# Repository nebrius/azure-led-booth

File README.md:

# Azure LED Booth

An LED art piece for conference booths that attendees can control from Azure. This project is, in part, based on @nebrius [Raver Lights](https://github.com/nebrius/raver-lights) project.

This project touches on a few other repos of interest:

- https://github.com/nebrius/rvl-node-animations A helper library for creating animations
- TODO: starter repo link

# License

MIT License

Copyright (c) Bryan Hughes <bryan@nebri.us>

Permission is hereby granted, free of charge, to any person obtaining a copy
of this software and associated documentation files (the "Software"), to deal
in the Software without restriction, including without limitation the rights
to use, copy, modify, merge, publish, distribute, sublicense, and/or sell
copies of the Software, and to permit persons to whom the Software is
furnished to do so, subject to the following conditions:

The above copyright notice and this permission notice shall be included in all
copies or substantial portions of the Software.

THE SOFTWARE IS PROVIDED "AS IS", WITHOUT WARRANTY OF ANY KIND, EXPRESS OR
IMPLIED, INCLUDING BUT NOT LIMITED TO THE WARRANTIES OF MERCHANTABILITY,
FITNESS FOR A PARTICULAR PURPOSE AND NONINFRINGEMENT. IN NO EVENT SHALL THE
AUTHORS OR COPYRIGHT HOLDERS BE LIABLE FOR ANY CLAIM, DAMAGES OR OTHER
LIABILITY, WHETHER IN AN ACTION OF CONTRACT, TORT OR OTHERWISE, ARISING FROM,
OUT OF OR IN CONNECTION WITH THE SOFTWARE OR THE USE OR OTHER DEALINGS IN THE
SOFTWARE.

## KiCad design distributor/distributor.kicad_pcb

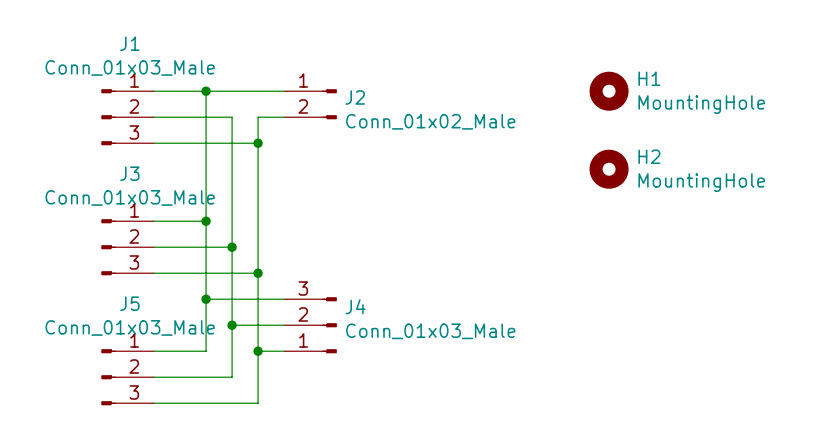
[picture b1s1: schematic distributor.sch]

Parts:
H1, H2: MountingHole; MountingHole_3.7mm
J1, J3, J5: Conn_01x03_Male; JST_VH_S3P-VH_1x03_P3.96mm_Horizontal
J2: Conn_01x02_Male; JST_VH_S2P-VH_1x02_P3.96mm_Horizontal
J4: Conn_01x03_Male; PinHeader_1x03_P2.54mm_Horizontal

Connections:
unnamed: J1.1, J2.1, J3.1, J4.3, J5.1
unnamed: J1.2, J3.2, J4.2, J5.2
unnamed: J1.3, J2.2, J3.3, J4.1, J5.3

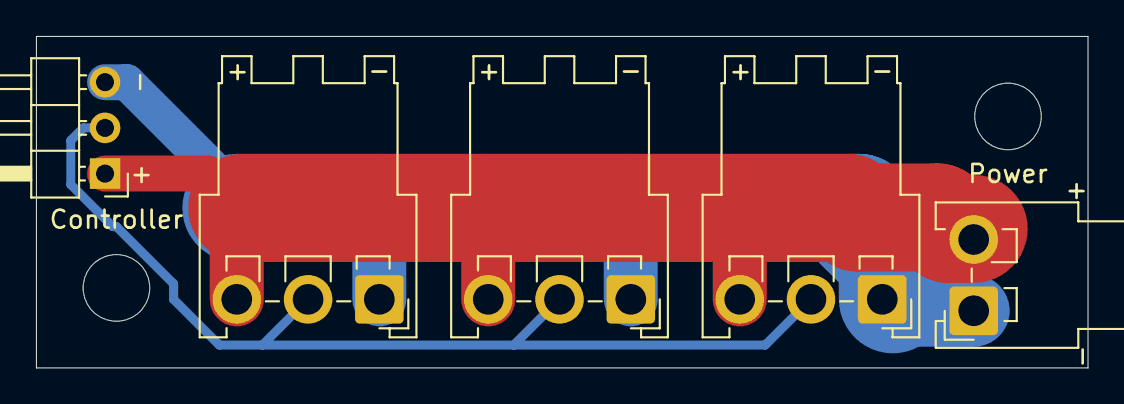
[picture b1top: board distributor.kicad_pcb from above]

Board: 2 copper layers, 58.4 x 18.4 mm, 7 parts (0 on the bottom side), 3 nets.

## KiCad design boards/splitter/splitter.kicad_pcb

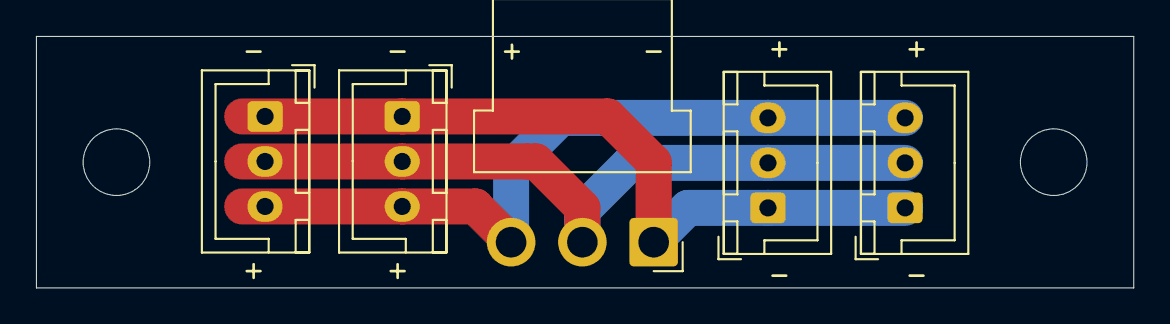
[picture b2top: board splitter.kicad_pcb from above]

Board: 2 copper layers, 61.0 x 14.0 mm, 7 parts (0 on the bottom side), 3 nets.

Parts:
H1, H2: MountingHole; MountingHole_3.7mm
J1, J2, J4, J5: Conn_01x03_Male; JST_XH_B3B-XH-A_1x03_P2.50mm_Vertical
J3: Conn_01x03_Male; JST_VH_B3PS-VH_1x03_P3.96mm_Horizontal

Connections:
unnamed: J1.1, J2.1, J3.1, J4.1, J5.1
unnamed: J1.2, J2.2, J3.2, J4.2, J5.2
unnamed: J1.3, J2.3, J3.3, J4.3, J5.3

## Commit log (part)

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2019-02-28 Create LICENSE
2019-02-28 file cleanup
2019-02-28 Added Raver Lights link
2019-03-25 Started working on design doc
2019-03-25 Finished first draft of the design doc
2019-04-11 Added physical designs for the box
2019-04-11 Added RPi to the BOM
2019-04-12 Shrunk dimensions of the base
2019-04-15 Designed and ordered v1.0 of the distributor and splitter boards
2019-04-18 Updated dimensions of the LED object
2019-05-06 Scaffolded out the various code pieces
2019-05-06 Fleshed out Functions build infrastructure
2019-05-06 Created an animation interface (for the controller)
2019-05-06 Cleaned up all the builds
2019-05-06 Removed example as it'll live in a separate clonable repo
2019-05-06 First draft of the device code
2019-05-07 Started fleshing out Functions details
2019-05-07 created deploy script
2019-05-08 Started dabbling in Functions code
2019-05-08 Fleshed out functions a bit more
2019-05-10 Got basic submission function working!
2019-05-10 Finished custom submissions and getting the queue
2019-05-10 Added stricter checking for custom submissions
2019-05-15 Scaffolded timer function
2019-05-16 Theoretically implemented basic animation support
2019-05-16 Refactored some things...I don't remember what cause wine, but TypeScript says it's ok
2019-05-16 Implemented much of the infrastructure for basic animation processing
2019-05-16 In theory the backend works
2019-05-16 Cleaned up some error handling
2019-05-16 First draft of device
2019-05-16 Removed launch.json from version control so I can add API keys to it
2019-05-16 Created instructions for setting up the Raspberry Pi
2019-05-16 Made the default animation prettier
2019-05-17 Implemented build and deploy infrastructure for clients
2019-05-21 Created basic scaffolding in React
2019-05-21 Created UI structre
2019-05-21 Switched to a single codebase for each client w/ multiple webpack entry points
2019-05-21 Fixed deploy
2019-05-21 Added dev/prod builds
2019-05-21 Fixed source maps
2019-05-22 Changed auth level
2019-05-22 Worked out some deployment and production build issues
2019-05-22 Fixed the return values from the get-queue function
2019-05-22 Implemented rudimentary queue viewing
2019-05-22 Cleaned up queue display
2019-05-22 Bug fixes and got basic submission working
2019-05-22 I...I think the clients are finished
2019-05-22 Scaffolded simulator
2019-05-22 Implemented simulation backend (woa that was easy!)
2019-05-22 Cleaned up controls display
2019-05-22 Finished LED object layout
2019-05-23 Got a lot of the simulator running, but the algorithm is broken. Gonna have to use WASM
2019-05-23 Slight tweakts to the simulator
2019-05-24 First stab at web assembly
2019-05-24 WASM works!! Although animations are still broken? Weird
2019-05-24 Tweaks
2019-05-24 Fixed one (of two?) bugs in rendering
2019-05-24 Minor bug fixes
2019-05-25 Implemented stats gathering
2019-05-25 Implemented API key support
2019-05-26 Refactoring and bug fixes
2019-05-26 Added save banner to clients
2019-05-26 Added submission type to queue display
2019-05-27 Added better error handling to simulator
2019-05-27 Added a lot of logging
2019-05-31 Increased animation time and added client banner timeouts
2019-05-31 Added links to headers
2019-05-31 Rewrote process-queue to use a more advanced HTTP-based mechanism
2019-05-31 ok now it works
2020-03-14 Bump acorn from 6.1.1 to 6.4.1 in /clients
    Bumps [acorn](https://github.com/acornjs/acorn) from 6.1.1 to 6.4.1.
    - [Release notes](https://github.com/acornjs/acorn/releases)
    - [Commits](https://github.com/acornjs/acorn/compare/6.1.1...6.4.1)
2020-07-30 Bump elliptic from 6.4.1 to 6.5.3 in /clients
    Bumps [elliptic](https://github.com/indutny/elliptic) from 6.4.1 to 6.5.3.
    - [Release notes](https://github.com/indutny/elliptic/releases)
    - [Commits](https://github.com/indutny/elliptic/compare/v6.4.1...v6.5.3)
2020-09-08 Bump http-proxy from 1.17.0 to 1.18.1 in /clients
    Bumps [http-proxy](https://github.com/http-party/node-http-proxy) from 1.17.0 to 1.18.1.
    - [Release notes](https://github.com/http-party/node-http-proxy/releases)
    - [Changelog](https://github.com/http-party/node-http-proxy/blob/master/CHANGELOG.md)
    - [Commits](https://github.com/http-party/node-http-proxy/compare/1.17.0...1.18.1)
2020-09-11 Bump node-fetch from 2.6.0 to 2.6.1 in /functions
    Bumps [node-fetch](https://github.com/bitinn/node-fetch) from 2.6.0 to 2.6.1.
    - [Release notes](https://github.com/bitinn/node-fetch/releases)
    - [Changelog](https://github.com/node-fetch/node-fetch/blob/master/docs/CHANGELOG.md)
    - [Commits](https://github.com/bitinn/node-fetch/compare/v2.6.0...v2.6.1)
2020-12-11 Bump ini from 1.3.5 to 1.3.7 in /clients
    Bumps [ini](https://github.com/isaacs/ini) from 1.3.5 to 1.3.7.
    - [Release notes](https://github.com/isaacs/ini/releases)
    - [Commits](https://github.com/isaacs/ini/compare/v1.3.5...v1.3.7)
2021-03-09 Bump elliptic from 6.4.1 to 6.5.4 in /clients
    Bumps [elliptic](https://github.com/indutny/elliptic) from 6.4.1 to 6.5.4.
    - [Release notes](https://github.com/indutny/elliptic/releases)
    - [Commits](https://github.com/indutny/elliptic/compare/v6.4.1...v6.5.4)
2021-03-30 Bump y18n from 4.0.0 to 4.0.1 in /clients
    Bumps [y18n](https://github.com/yargs/y18n) from 4.0.0 to 4.0.1.
    - [Release notes](https://github.com/yargs/y18n/releases)
    - [Changelog](https://github.com/yargs/y18n/blob/master/CHANGELOG.md)
    - [Commits](https://github.com/yargs/y18n/commits)
2021-04-20 Bump ssri from 6.0.1 to 6.0.2 in /clients
    Bumps [ssri](https://github.com/npm/ssri) from 6.0.1 to 6.0.2.
    - [Release notes](https://github.com/npm/ssri/releases)
    - [Changelog](https://github.com/npm/ssri/blob/v6.0.2/CHANGELOG.md)
    - [Commits](https://github.com/npm/ssri/compare/v6.0.1...v6.0.2)
2021-05-10 Bump hosted-git-info from 2.7.1 to 2.8.9 in /clients
    Bumps [hosted-git-info](https://github.com/npm/hosted-git-info) from 2.7.1 to 2.8.9.
    - [Release notes](https://github.com/npm/hosted-git-info/releases)
    - [Changelog](https://github.com/npm/hosted-git-info/blob/v2.8.9/CHANGELOG.md)
    - [Commits](https://github.com/npm/hosted-git-info/compare/v2.7.1...v2.8.9)
2021-08-11 Bump path-parse from 1.0.6 to 1.0.7 in /clients
    Bumps [path-parse](https://github.com/jbgutierrez/path-parse) from 1.0.6 to 1.0.7.
    - [Release notes](https://github.com/jbgutierrez/path-parse/releases)
    - [Commits](https://github.com/jbgutierrez/path-parse/commits/v1.0.7)
    ---
    updated-dependencies:
    - dependency-name: path-parse
2022-01-22 Bump node-fetch from 2.6.0 to 3.1.1 in /functions
    Bumps [node-fetch](https://github.com/node-fetch/node-fetch) from 2.6.0 to 3.1.1.
    - [Release notes](https://github.com/node-fetch/node-fetch/releases)
    - [Changelog](https://github.com/node-fetch/node-fetch/blob/main/docs/CHANGELOG.md)
    - [Commits](https://github.com/node-fetch/node-fetch/compare/v2.6.0...v3.1.1)
    ---
    updated-dependencies:
2022-01-22 Bump node-fetch from 2.6.0 to 3.1.1 in /device
    Bumps [node-fetch](https://github.com/node-fetch/node-fetch) from 2.6.0 to 3.1.1.
    - [Release notes](https://github.com/node-fetch/node-fetch/releases)
    - [Changelog](https://github.com/node-fetch/node-fetch/blob/main/docs/CHANGELOG.md)
    - [Commits](https://github.com/node-fetch/node-fetch/compare/v2.6.0...v3.1.1)
    ---
    updated-dependencies:
2022-02-11 Bump ajv from 6.10.0 to 6.12.6 in /clients
    Bumps [ajv](https://github.com/ajv-validator/ajv) from 6.10.0 to 6.12.6.
    - [Release notes](https://github.com/ajv-validator/ajv/releases)
    - [Commits](https://github.com/ajv-validator/ajv/compare/v6.10.0...v6.12.6)
    ---
    updated-dependencies:
    - dependency-name: ajv
2022-02-12 Bump node-fetch from 2.6.0 to 2.6.7 in /functions
    Bumps [node-fetch](https://github.com/node-fetch/node-fetch) from 2.6.0 to 2.6.7.
    - [Release notes](https://github.com/node-fetch/node-fetch/releases)
    - [Commits](https://github.com/node-fetch/node-fetch/compare/v2.6.0...v2.6.7)
    ---
    updated-dependencies:
    - dependency-name: node-fetch
2022-02-12 Bump node-fetch from 2.6.0 to 2.6.7 in /device
    Bumps [node-fetch](https://github.com/node-fetch/node-fetch) from 2.6.0 to 2.6.7.
    - [Release notes](https://github.com/node-fetch/node-fetch/releases)
    - [Commits](https://github.com/node-fetch/node-fetch/compare/v2.6.0...v2.6.7)
    ---
    updated-dependencies:
    - dependency-name: node-fetch
2022-02-12 Bump follow-redirects from 1.7.0 to 1.14.8 in /clients
    Bumps [follow-redirects](https://github.com/follow-redirects/follow-redirects) from 1.7.0 to 1.14.8.
    - [Release notes](https://github.com/follow-redirects/follow-redirects/releases)
    - [Commits](https://github.com/follow-redirects/follow-redirects/compare/v1.7.0...v1.14.8)
    ---
    updated-dependencies:
    - dependency-name: follow-redirects
2022-12-03 Bump decode-uri-component from 0.2.0 to 0.2.2 in /clients
    Bumps [decode-uri-component](https://github.com/SamVerschueren/decode-uri-component) from 0.2.0 to 0.2.2.
    - [Release notes](https://github.com/SamVerschueren/decode-uri-component/releases)
    - [Commits](https://github.com/SamVerschueren/decode-uri-component/compare/v0.2.0...v0.2.2)
    ---
    updated-dependencies:
    - dependency-name: decode-uri-component
2022-12-06 Bump qs and http-server in /clients
    Bumps [qs](https://github.com/ljharb/qs) to 6.11.0 and updates ancestor dependency [http-server](https://github.com/http-party/http-server). These dependencies need to be updated together.
    Updates `qs` from 2.3.3 to 6.11.0
    - [Release notes](https://github.com/ljharb/qs/releases)
    - [Changelog](https://github.com/ljharb/qs/blob/main/CHANGELOG.md)
    - [Commits](https://github.com/ljharb/qs/compare/v2.3.3...v6.11.0)
    Updates `http-server` from 0.11.1 to 0.11.2
2023-01-01 Bump json5, ts-loader, webpack and webpack-cli in /clients
    Removes [json5](https://github.com/json5/json5). It's no longer used after updating ancestor dependencies [json5](https://github.com/json5/json5), [ts-loader](https://github.com/TypeStrong/ts-loader)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
    Removes `json5`
    Updates `ts-loader` from 5.3.3 to 9.4.2
    - [Release notes](https://github.com/TypeStrong/ts-loader/releases)
    - [Changelog](https://github.com/TypeStrong/ts-loader/blob/main/CHANGELOG.md)
    - [Commits](https://github.com/TypeStrong/ts-loader/compare/v5.3.3...v9.4.2)
2023-01-07 Bump json5 from 1.0.1 to 1.0.2 in /clients
    Bumps [json5](https://github.com/json5/json5) from 1.0.1 to 1.0.2.
    - [Release notes](https://github.com/json5/json5/releases)
    - [Changelog](https://github.com/json5/json5/blob/main/CHANGELOG.md)
    - [Commits](https://github.com/json5/json5/compare/v1.0.1...v1.0.2)
    ---
    updated-dependencies:
2023-02-28 Bump minimist and mkdirp in /device
    Bumps [minimist](https://github.com/minimistjs/minimist) and [mkdirp](https://github.com/isaacs/node-mkdirp). These dependencies needed to be updated together.
    Updates `minimist` from 1.2.0 to 1.2.8
    - [Release notes](https://github.com/minimistjs/minimist/releases)
    - [Changelog](https://github.com/minimistjs/minimist/blob/main/CHANGELOG.md)
    - [Commits](https://github.com/minimistjs/minimist/compare/v1.2.0...v1.2.8)
    Updates `mkdirp` from 0.5.1 to 0.5.6

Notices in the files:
boards/splitter/splitter.kicad_pcb:
Raver Lights Splitter v1.0 Copyright Bryan Hughes 2019
distributor/distributor.kicad_pcb:
Raver Lights Distributer v1.0 Copyright Bryan Hughes 2019
